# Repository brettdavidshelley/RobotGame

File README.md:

# RobotGame
Luke Pearson, Brett Shelley, Damion Mejia
ECE3011 | Spring 2025

GT Junior Design Project - Education Math and Music Game

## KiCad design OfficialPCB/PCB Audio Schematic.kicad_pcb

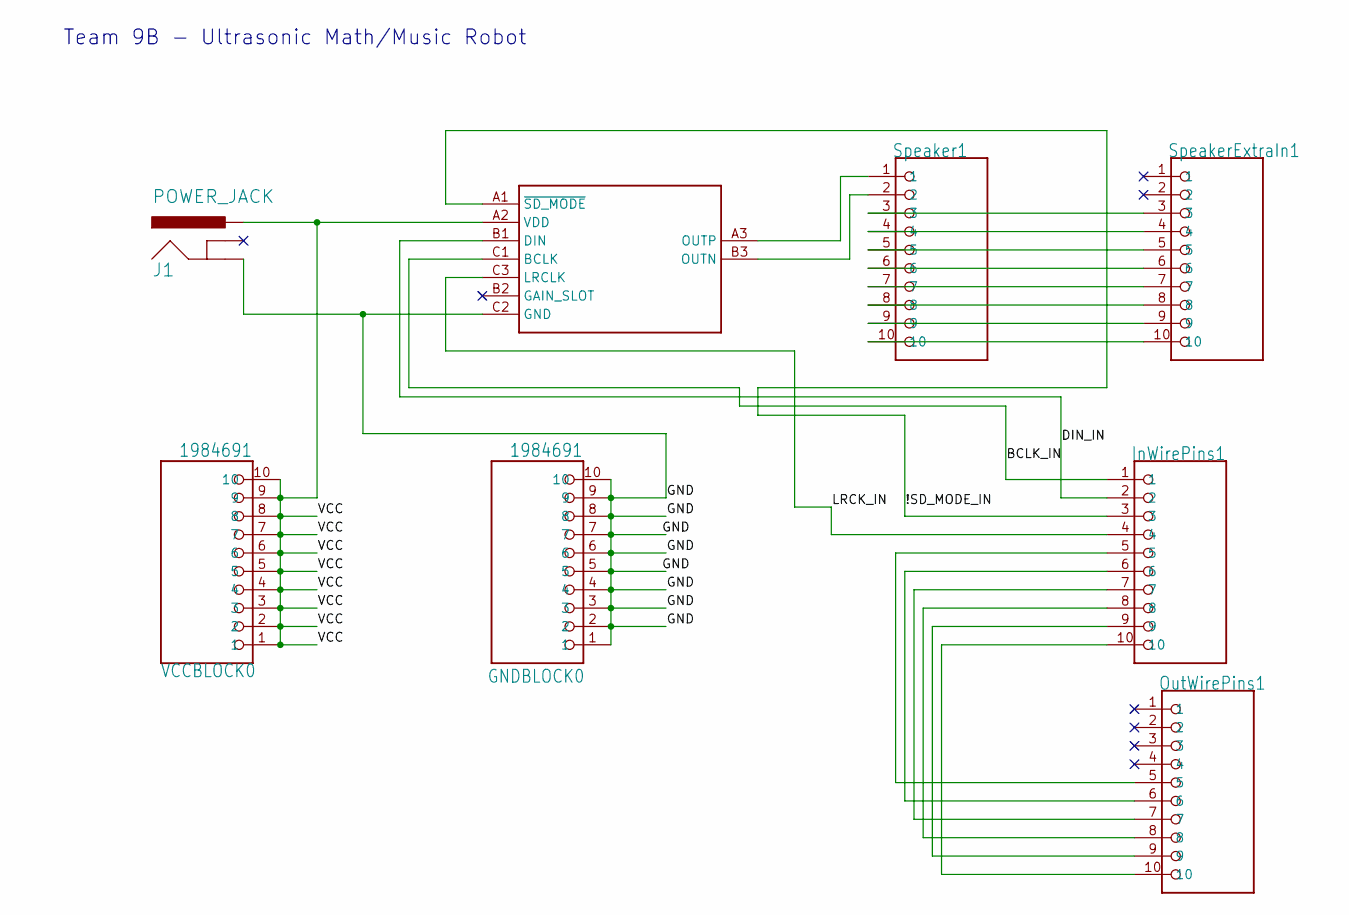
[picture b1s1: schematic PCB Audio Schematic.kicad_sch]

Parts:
GNDBLOCK0: 1984691; PHOENIX_1984691
InWirePins1: PHOENIX_1984691
J1: POWER_JACK
OutWirePins1: PHOENIX_1984691
Speaker1: PHOENIX_1984691
SpeakerExtraIn1: PHOENIX_1984691
U1: MAX98357A
VCCBLOCK0: 1984691; PHOENIX_1984691

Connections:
/!SD_MODE_IN: InWirePins1.3, U1.A1 (~SD_MODE)
/BCLK_IN: InWirePins1.1, U1.C1 (BCLK)
/DIN_IN: InWirePins1.2, U1.B1 (DIN)
/GND: GNDBLOCK0.1, GNDBLOCK0.2, GNDBLOCK0.3, GNDBLOCK0.4, GNDBLOCK0.5, GNDBLOCK0.6, GNDBLOCK0.7, GNDBLOCK0.8, GNDBLOCK0.9, GNDBLOCK0.10, J1.GND, U1.C2 (GND)
/LRCK_IN: InWirePins1.4, U1.C3 (LRCLK)
/VCC: J1.PWR, U1.A2 (VDD), VCCBLOCK0.1, VCCBLOCK0.2, VCCBLOCK0.3, VCCBLOCK0.4, VCCBLOCK0.5, VCCBLOCK0.6, VCCBLOCK0.7, VCCBLOCK0.8, VCCBLOCK0.9, VCCBLOCK0.10
unnamed: InWirePins1.5, OutWirePins1.5
unnamed: InWirePins1.6, OutWirePins1.6
unnamed: InWirePins1.7, OutWirePins1.7
unnamed: InWirePins1.8, OutWirePins1.8
unnamed: InWirePins1.9, OutWirePins1.9
unnamed: InWirePins1.10, OutWirePins1.10
unnamed: Speaker1.3, SpeakerExtraIn1.3
unnamed: Speaker1.4, SpeakerExtraIn1.4
unnamed: Speaker1.5, SpeakerExtraIn1.5
unnamed: Speaker1.6, SpeakerExtraIn1.6
unnamed: Speaker1.7, SpeakerExtraIn1.7
unnamed: Speaker1.8, SpeakerExtraIn1.8
unnamed: Speaker1.9, SpeakerExtraIn1.9
unnamed: Speaker1.10, SpeakerExtraIn1.10
unnamed: Speaker1.2, U1.B3 (OUTN)
unnamed: Speaker1.1, U1.A3 (OUTP)

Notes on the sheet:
Team 9B - Ultrasonic Math/Music Robot

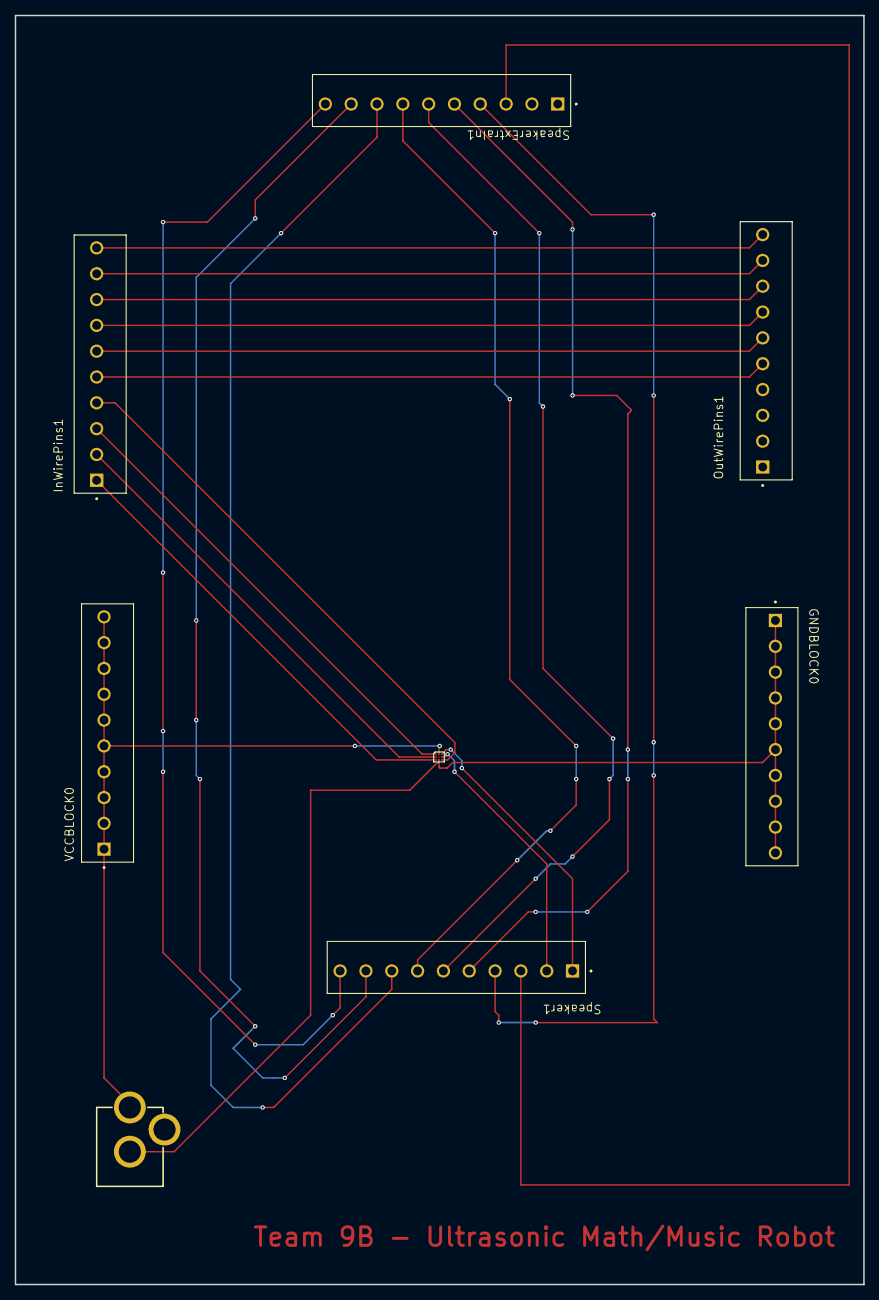
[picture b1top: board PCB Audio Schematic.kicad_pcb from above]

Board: 2 copper layers, 115.0 x 172.0 mm, 8 parts (0 on the bottom side), 22 nets.

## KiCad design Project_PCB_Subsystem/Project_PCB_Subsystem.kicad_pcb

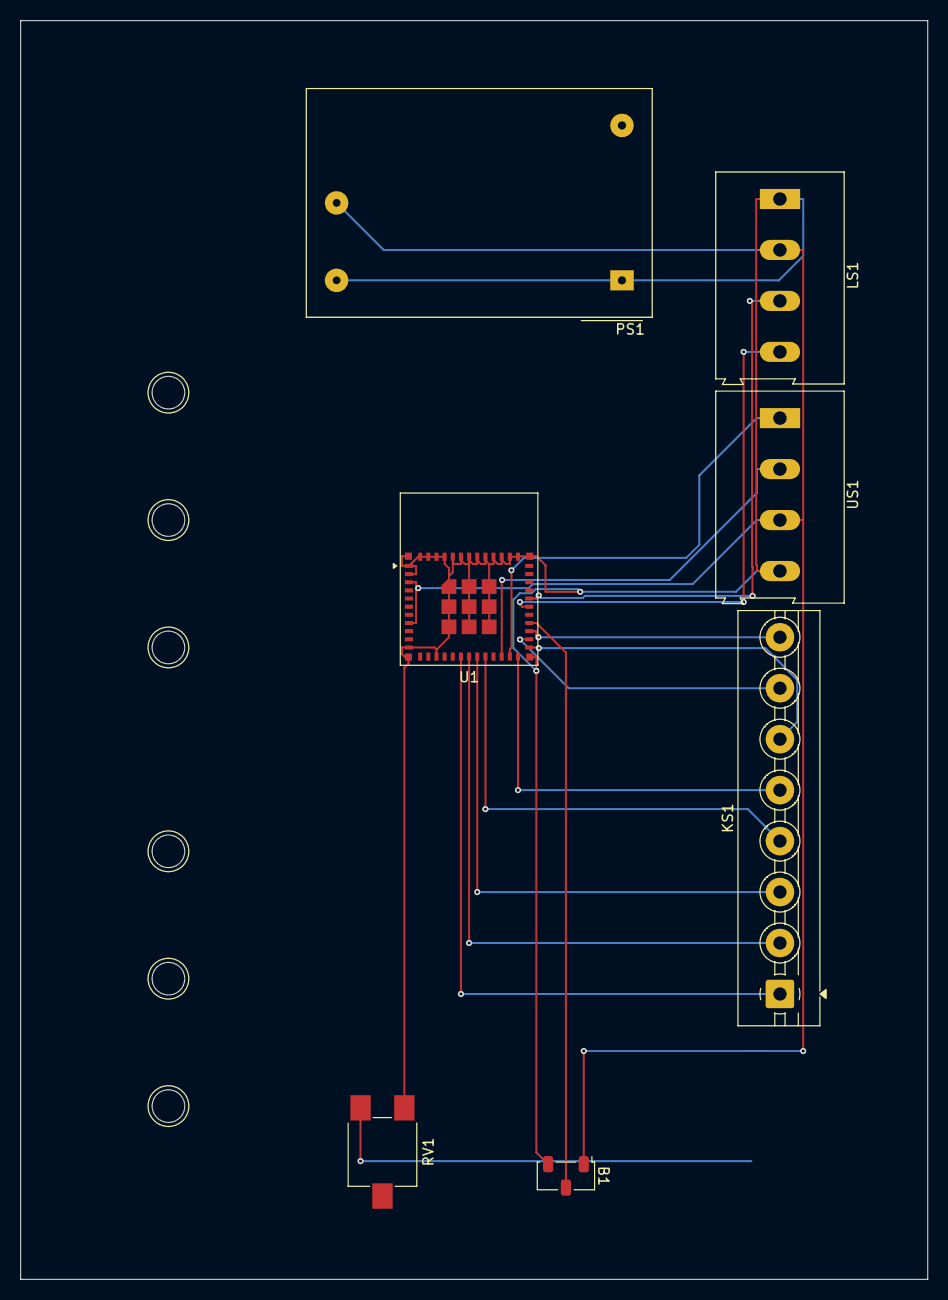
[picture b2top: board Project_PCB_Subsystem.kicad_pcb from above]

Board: 2 copper layers, 89.0 x 123.5 mm, 10 parts (1 on the bottom side), 16 nets.

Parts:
B1: ButtonSwitch; Nidec_Copal_CAS-120A
KS1: 4x4Keypad_ScrewTerminal; TerminalBlock_MaiXu_MX126-5.0-08P_1x08_P5.00mm
LS1: LCD_ScrewTerminal; TerminalBlock_Altech_AK300-4_P5.00mm
MS1, MS2: Motor_Servo; DINRailAdapter_3xM3_PhoenixContact_1201578
PS1: IRM-02-3.3; Converter_ACDC_MeanWell_IRM-02-xx_THT
RV1: R_Potentiometer; Potentiometer_ACP_CA6-VSMD_Vertical
SPK1: Speaker; Speaker_CUI_CMR-1206S-67
U1: ESP32-C6 Microcontroller; ESP32-C6-MINI-1
US1: Sensor_ScrewTerminal; TerminalBlock_Altech_AK300-4_P5.00mm

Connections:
GND: B1.3 (A), LS1.1, PS1.1 (AC/N), PS1.3 (-Vo), RV1.3, U1.1 (GND), U1.2 (GND), U1.11 (GND), U1.14 (GND), U1.36 (GND), U1.37 (GND), U1.38 (GND), U1.39 (GND), U1.40 (GND), U1.41 (GND), U1.42 (GND), U1.43 (GND), U1.44 (GND), U1.45 (GND), U1.46 (GND), U1.47 (GND), U1.48 (GND), U1.49 (GND), U1.50 (GND), U1.51 (GND), U1.52 (GND), U1.53 (GND), US1.4
unnamed: B1.2 (B), U1.28 (IO22)
unnamed: KS1.1, U1.17 (IO12)
unnamed: KS1.2, U1.18 (IO13)
unnamed: KS1.3, U1.19 (IO14)
unnamed: KS1.4, U1.20 (IO15)
unnamed: KS1.5, U1.24 (IO18)
unnamed: KS1.6, U1.25 (IO19)
unnamed: KS1.7, U1.26 (IO20)
unnamed: KS1.8, U1.27 (IO21)
unnamed: LS1.3, U1.31 (TXD0)
unnamed: LS1.4, U1.30 (RXD0)
unnamed: RV1.1, SPK1.1
unnamed: U1.22 (IO8), US1.2
unnamed: U1.23 (IO9), US1.1
VCC: B1.1 (C), LS1.2, PS1.4 (+Vo), SPK1.2, U1.3 (3V3), U1.8 (EN), US1.3

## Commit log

2025-01-26 Initialized PlatformIO project for the ESP32-C6-DevKitC-1
2025-01-26 Initialized .cpp files with espidf framework
2025-01-30 Started on keypad/UART LCD code in main.cpp. Currently untested. Also included a firmware zip file I found online
2025-01-30 Improvements
2025-02-04 Need to reclone
2025-02-04 Quick LCD Clear fix
2025-02-04 Added current Arduino-style code format. Clearing and setting cursor does not work on the LCD for some reason.
2025-02-05 Progress on the entire system
2025-02-05 Compiles in Arduino IDE
2025-02-07 Added PCB_Project files.
    1.) Assigned footprints may need to be reconfigured.
    2.) DRC has not been passed, need to route paths/vias. I suggest finding an Autoroute plugin if using KiCAD.
2025-02-08 Updated PCB design file folder
2025-02-11 Improvements
    1.) Switched to I2C to communicate with the LCD.
    2.) Added more comments
2025-02-13 Continued implementation of both games.
    1.) Began implementing logic for correct/incorrect answers that interact with the servos and the speaker.
    2.) Accounted for negative numbers in math.
    3.) Implemented a cm to frequency converter function in music.
    4.) Re-arranged global variables.
2025-02-15 More progress. Issues with the button working conssitently for some reason.
2025-02-15 Added score tracking functionality. Still cannot get the button to work even with different pins for some reason.
2025-02-15 Math game complete.
2025-02-16 Efficiency improvements to main and progress on music. Ready to test with sensor components
2025-02-17 Cursor fix
2025-02-20 Create Audio Test Code initial
    This was the initial code that was used for my speaker to play a sound
2025-02-21 Speaker integrated.
2025-02-22 Cursor improvements
2025-02-25 Software essentially completed.
    1.) Integrated HCSR04 Ultrasonic Sensor
    2.) Integrated the two servos.
    3.) Tested all gameplay for smoothness and functionality.
    There may be some very minor quality-of-life value tweaking needed in the future, but this is essentially the finished product.
2025-02-25 Slight tweaks + more comments and prettification
2025-03-03 CAD Files
    Some final PCB stuff and some new 3D modeling stuff
2025-04-02 Tweaked servo nodding values
